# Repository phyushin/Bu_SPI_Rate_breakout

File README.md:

# Bu_SPI_Rate_breakout
Schematics for an SPI Breakout board for the bus pirate
V0.1
Added Headers for BP3 and BP4 as well as voltage selection.

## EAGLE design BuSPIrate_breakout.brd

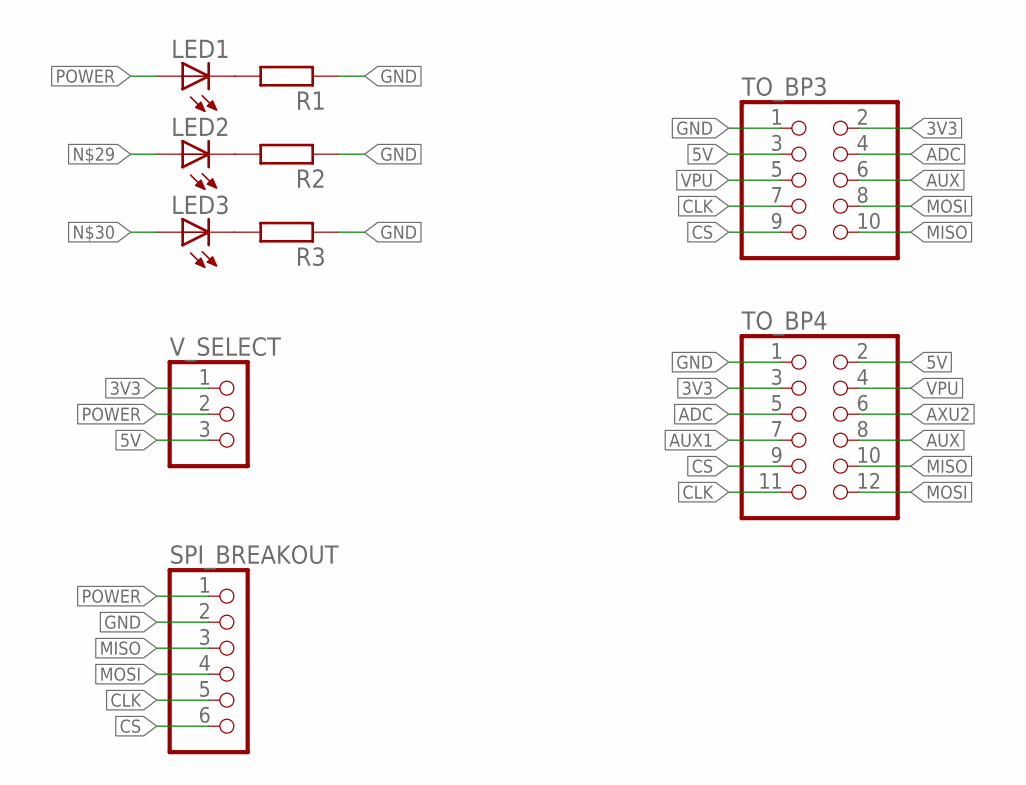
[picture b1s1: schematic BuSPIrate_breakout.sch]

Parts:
LED1, LED2, LED3: LEDSML1206; SML1206
R1, R2, R3: R-EU_M1206; M1206
SPI_BREAKOUT: PINHD-1X6; 1X06
TO_BP3: PINHD-2X5; 2X05
TO_BP4: PINHD-2X6; 2X06
V_SELECT: PINHD-1X3; 1X03

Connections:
3V3: TO_BP3.2, TO_BP4.3, V_SELECT.1
5V: TO_BP3.3, TO_BP4.2, V_SELECT.3
ADC: TO_BP3.4, TO_BP4.5
AUX: TO_BP3.6, TO_BP4.8
AUX1: TO_BP4.7
AXU2: TO_BP4.6
CLK: SPI_BREAKOUT.5, TO_BP3.7, TO_BP4.11
CS: SPI_BREAKOUT.6, TO_BP3.9, TO_BP4.9
GND: R1.1, R2.1, R3.1, SPI_BREAKOUT.2, TO_BP3.1, TO_BP4.1
MISO: SPI_BREAKOUT.3, TO_BP3.10, TO_BP4.10
MOSI: SPI_BREAKOUT.4, TO_BP3.8, TO_BP4.12
unnamed: LED1.C, R1.2
unnamed: LED2.C, R2.2
unnamed: LED3.C, R3.2
POWER: LED1.A, SPI_BREAKOUT.1, V_SELECT.2
VPU: TO_BP3.5, TO_BP4.4

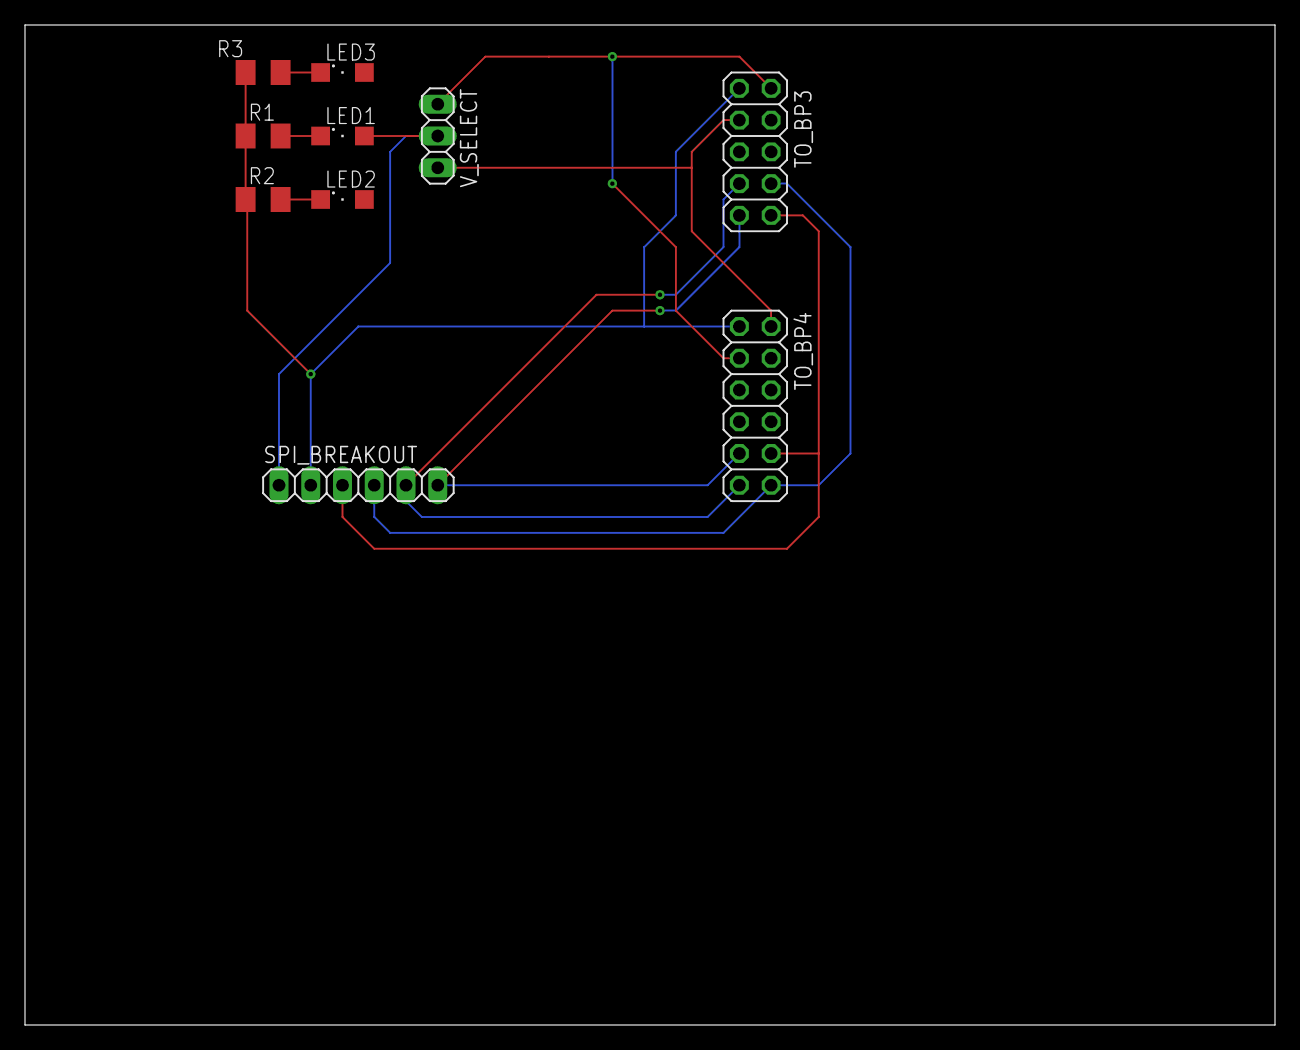
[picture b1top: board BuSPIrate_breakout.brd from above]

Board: 2 copper layers, 100.0 x 80.0 mm, 10 parts (0 on the bottom side), 14 nets.

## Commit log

2019-02-10 added schematic and board files
